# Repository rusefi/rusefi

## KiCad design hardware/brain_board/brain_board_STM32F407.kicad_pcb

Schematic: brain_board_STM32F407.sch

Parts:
BT1: BATTERY_CR2032; BATT_CR2032_MPD
C1: 20nF; C_0805
C2, C3, C21, C22: 18pF; C_0805
C4, C15, C17: 2u2F; C_0805
C5, C8: 0.01uF; C_0805
C6, C7, C16: 1uF; C_0805
C9, C10, C11, C12, C13, C14, C18, C20: 0.1uF; C_0805
C19: 4.7uF; C_0805
D1, D2, D3, D4, D7, D8, D11: BLUE_LED_0805; LED_0805
D5, D6, D9: PMEG2010EA; D_0805
F1002: FUSE; D_0805
FB1: FILTER; R_0805
G1: LOGO; LOGO_F
J1: MINI-USB-5P-3400020P1
J2: MINI-USB-5P-3400020P1V; MINI-USB_RCTP_V-T_B
JP1, JP2, JP3, JP4: JUMPER; Pin_Header_Straight_1x02_Pitch2.54mm
JP5: JUMPER3; Pin_Header_Straight_1x03_Pitch2.54mm
P1, P2: CONN_25X2; Pin_Header_Straight_2x25_Pitch2.54mm
P3: CONN_2; Pin_Header_Straight_1x02_Pitch2.54mm
P4: CONN_02X05; IDC_Header_Straight_10pins
P5, P6: CONN_01X03; Pin_Header_Angled_1x03
R1, R3, R4: 10k; R_0805
R2: 100R; R_0805
R5: 330R; R_0805
R6, R7, R8, R9: 680R; R_0805
R10: 47R; R_0805
R11, R12, R13: 1k; R_0805
R14: 100k; R_0805
SW1, SW2: SW_PUSH; TL-1105
U1: STM32F407VG; LQFP-100_14x14mm_Pitch0.5mm
U2: NUF2101MT1G; SOT-457
U3: LM2937; SOT223
X1: CRYSTAL; HC-49V
X2: CRYSTAL(MC306); MC-306

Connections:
/3V: D9.2 (K), P2.5, P2.6
/5V: C18.2, C19.1, D5.2 (K), D6.2 (K), F1002.1, F1002.2, P2.3, P2.4, P4.1, P4.2, U3.1 (Vin)
/BOOT0: P2.21, R4.2, U1.94 (BOOT0)
/D+: J1.3 (D+), J2.3 (D+), U2.6 (D+)
/D-: J1.2 (D-), J2.2 (D-), U2.4 (D-)
/NRST: C1.2, P1.6, P4.9, R3.2, SW1.1, U1.14 (NRST)
/PA0: P1.12, R5.1, U1.23 (PA0/WKUP/USART2_CTS/UART4_TX/ETH_MII_CR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)
/PA1: P1.11, U1.24 (PA1/USART2_RTS/UART4_RX/ETH_RMII_REF_CL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)
/PA2: P1.14, U1.25 (PA2/USART2_TX/TIM5_CH3/TIM9_CH1/TIM2_CH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)
/PA3: P1.13, U1.26 (PA3/USART2_RX/TIM5_CH4/TIM9_CH2/TIM2_CH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)
/PA4: P1.16, U1.29 (PA4/SPI1_NSS/SPI3_NSS/USART2_CK/DCMI_HS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)
/PA5: P1.15, U1.30 (PA5/SPI1_SCK/OTG_HS_ULPI_CK/TIM2_CH1_ET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)
/PA6: P1.18, U1.31 (PA6/SPI1_MISO/TIM8_BKIN/TIM13_CH1/DCMI_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)
/PA7: P1.17, U1.32 (PA7/SPI1_MOSI/TIM8_CH1N/TIM14_CH1/TIM3_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)
/PA8: P2.43, U1.67 (PA8/MCO1/USART1_CK/TIM1_CH1/I2C3_SCL/OT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)
/PA9: D6.1 (A), J1.1 (VBUS), J2.1 (VBUS), P2.44, R12.2, U1.68 (PA9/USART1_TX/TIM1_CH2/I2C3_SMBA/DCMI_D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), U2.5 (Vbus)
/PA10: P2.41, U1.69 (PA10/USART1_RX/TIM1_CH3/OTG_FS_ID/DCMI_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)
/PA11: U1.70 (PA11/USART1_CTS/CAN1_RX/TIM1_CH4_/OTG_F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), U2.3 (D-out)
/PA12: U1.71 (PA12/USART1_RTS/CAN1_TX/TIM1_ETR/OTG_FS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), U2.1 (D+out)
/PA13: P2.42, P4.10, U1.72 (PA13/JTMS/SWDIO/EVENTOUT)
/PA14: P2.39, P4.6, U1.76 (PA14/JTCK/SWCLK/EVENTOUT)
/PA15: P2.40, U1.77 (PA15/JTDI/SPI3_NSS/I2S3_WS/TIM2_CH1_ETR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)
/PB0: P1.22, U1.35 (PB0/TIM3_CH3/TIM8_CH2N/OTG_HS_ULPI_D1/E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)
/PB1: P1.21, U1.36 (PB1/TIM3_CH4/TIM8_CH3N/OTG_HS_ULPI_D2/E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)
/PB2: P1.24, U1.37 (PB2/BOOT1/EVENTOUT)
/PB3: P2.28, P4.5, P6.3, U1.89 (PB3/JTDO/TRACESWO/SPI3_SCK/I2S3_CK/TIM2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)
/PB4: P2.25, P5.1, U1.90 (PB4/NJTRST/SPI3_MISO/TIM3_CH1/SPI1_MISO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)
/PB5: P2.26, P5.2, U1.91 (PB5/I2C1_SMBA/CAN2_RX/OTG_HS_ULPI_D7/ET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)
/PB6: P2.23, U1.92 (PB6/I2C1_SCL/TIM4_CH1/CAN2_TX/DCMI_D5/U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)
/PB7: P2.24, U1.93 (PB7/I2C1_SDA/FSMC_NL/DCMI_VSYNC/USART1_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)
/PB8: P2.19, U1.95 (PB8/TIM4_CH3/SDIO_D4/TIM10_CH1/DCMI_D6/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)
/PB9: P2.20, U1.96 (PB9/SPI2_NSS/I2S2_WS/TIM4_CH4/TIM11_CH1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)
/PB10: P1.34, U1.47 (PB10/SPI2_SCK/I2S2_CK/I2C2_SCL/USART3_T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)
/PB11: P1.35, U1.48 (PB11/I2C2_SDA/USART3_RX/OTG_HS_ULPI_D4/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)
/PB12: P1.36, U1.51 (PB12/SPI2_NSS/I2S2_WS/I2C2_SMBA/USART3_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)
/PB13: P1.37, U1.52 (PB13/SPI2_SCK/I2S2_CK/USART3_CTS/TIM1_C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)
/PB14: P1.38, U1.53 (PB14/SPI2_MISO/TIM1_CH2N/TIM12_CH1/OTG_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)
/PB15: P1.39, U1.54 (PB15/SPI2_MOSI/I2S2_SD/TIM1_CH3N/TIM8_C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)
/PC0: P1.8, U1.15 (PC0/OTG_HS_ULPI_STP/EVENTOUT)
/PC1: P1.7, U1.16 (PC1/ETH_MDC/_EVENTOUT)
/PC2: P1.10, U1.17 (PC2/SPI2_MISO/OTG_HS_ULPI_DIR/ETH_MII_T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)
/PC3: P1.9, U1.18 (PC3/SPI2_MOSI/I2S2_SD/OTG_HS_ULPI_NXT/E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)
/PC4: P1.20, U1.33 (PC4/ETH_RMII_RX_D0/ETH_MII_RX_D0/EVENTO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)
/PC5: P1.19, U1.34 (PC5/ETH_RMII_RX_D1/ETH_MII_RX_D1/EVENTO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)
/PC6: P2.47, U1.63 (PC6/I2S2_MCK/TIM8_CH1/SDIO_D6/USART6_TX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)
/PC7: P2.48, U1.64 (PC7/I2S3_MCK/TIM8_CH2/SDIO_D7/USART6_RX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)
/PC8: P2.45, U1.65 (PC8/TIM8_CH3/SDIO_D0/TIM3_CH3/USART6_CK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)
/PC9: P2.46, U1.66 (PC9/I2S_CKIN/MCO2/TIM8_CH4/SDIO_D1/I2C3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)
/PC10: P2.37, U1.78 (PC10/SPI3_SCK/I2S3_CK/UART4_TX/SDIO_D2/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)
/PC11: P2.38, U1.79 (PC11/UART4_RX/SPI3_MISO/SDIO_D3/DCMI_D4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)
/PC12: P2.35, U1.80 (PC12/UART5_TX/SDIO_CK/DCMI_D9/SPI3_MOSI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)
/PC13: P2.12, U1.7 (PC13/EVENTOUT)
/PD0: P2.36, U1.81 (PD0/FSMC_D2/CAN1_RX/EVENTOUT)
/PD1: P2.33, U1.82 (PD1/FSMC_D3/CAN1_TX/EVENTOUT)
/PD2: P2.34, U1.83 (PD2/TIM3_ETR/UART5_RX/SDIO_CMD/DCMI_D11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)
/PD3: P2.31, U1.84 (PD3/FSMC_CLK/USART2_CTS/EVENTOUT)
/PD4: P2.32, P6.2, U1.85 (PD4/FSMC_NOE/USART2_RTS/EVENTOUT)
/PD5: P2.29, U1.86 (PD5/FSMC_NWE/USART2_TX/EVENTOUT)
/PD6: P2.30, U1.87 (PD6/FSMC_NWAIT/USART2_RX/EVENTOUT)
/PD7: P2.27, U1.88 (PD7/USART2_CK/FSMC_NE1/FSMC_NCE2/EVENTO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)
/PD8: P1.40, U1.55 (PD8/FSMC_D13/USART3_TX/EVENTOUT)
/PD9: P1.41, U1.56 (PD9/FSMC_D14/USART3_RX/EVENTOUT)
/PD10: P1.42, U1.57 (PD10/FSMC_D15/USART3_CK/EVENTOUT)
/PD11: P1.43, U1.58 (PD11/FSMC_CLE/FSMC_A16/USART3_CTS/EVENT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)
/PD12: JP1.1, P1.44, U1.59 (PD12/FSMC_ALE/FSMC_A17/TIM4_CH1/USART3_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)
/PD13: JP2.1, P1.45, U1.60 (PD13/FSMC_A18/TIM4_CH2/EVENTOUT)
/PD14: JP3.1, P1.46, U1.61 (PD14/FSMC_D0/TIM4_CH3/EVENTOUT/_EVENTOUT)
/PD15: JP4.1, P1.47, U1.62 (PD15/FSMC_D1/TIM4_CH4/EVENTOUT)
/PE0: P2.17, U1.97 (PE0/TIM4_ETR/FSMC_NBL0/DCMI_D2/EVENTOUT)
/PE1: P2.18, U1.98 (PE1/FSMC_NBL1/DCMI_D3/EVENTOUT)
/PE2: P2.15, U1.1 (PE2/TRACECLK/FSMC_A23/ETH_MII_TXD3/EVEN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)
/PE3: P2.16, U1.2 (PE3/TRACED0/FSMC_A19/EVENTOUT)
/PE4: P2.13, U1.3 (PE4/TRACED1/FSMC_A20/DCMI_D4/EVENTOUT)
/PE5: P2.14, U1.4 (PE5/TRACED2/FSMC_A21/TIM9_CH1/DCMI_D6/E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)
/PE6: P2.11, U1.5 (PE6/TRACED3_/_FSMC_A22/TIM9_CH2/DCMI_D7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)
/PE7: P1.25, U1.38 (PE7/FSMC_D4/TIM1_ETR/EVENTOUT)
/PE8: P1.26, U1.39 (PE8/FSMC_D5/TIM1_CH1N/EVENTOUT)
/PE9: P1.27, U1.40 (PE9/FSMC_D6/TIM1_CH1/EVENTOUT)
/PE10: P1.28, U1.41 (PE10/FSMC_D7/TIM1_CH2N/EVENTOUT)
/PE11: P1.29, U1.42 (PE11/FSMC_D8/TIM1_CH2/EVENTOUT)
/PE12: P1.30, U1.43 (PE12/FSMC_D9/TIM1_CH3N/EVENTOUT)
/PE13: P1.31, U1.44 (PE13/FSMC_D10/TIM1_CH3/EVENTOUT)
/PE14: P1.32, U1.45 (PE14/FSMC_D11/TIM1_CH4/EVENTOUT)
/PE15: P1.33, U1.46 (PE15/FSMC_D12/TIM1_BKIN/EVENTOUT)
/Shield: C20.1, J1.6 (SHIELD), J2.6 (SHIELD), R14.1
/VDD: C4.1, C9.2, C10.2, C11.2, C12.2, C13.2, C14.2, C16.2, D9.1 (A), FB1.2, JP5.1, P1.3, P1.4, P2.22, P4.3, P4.4, P5.3, R3.1, R13.2, SW2.2, U1.11 (VDD), U1.19 (VDD), U1.28 (VDD), U1.50 (VDD), U1.75 (VDD), U1.100 (VDD), U3.3 (Vout)
GND: BT1.2 (-), C1.1, C2.2, C3.2, C5.1, C6.1, C7.1, C8.1, C9.1, C10.1, C11.1, C12.1, C13.1, C14.1, C15.2, C16.1, C17.2, C18.1, C19.2, C20.2, C21.1, C22.1, D1.2 (K), D2.2 (K), D3.2 (K), D4.2 (K), D7.2 (K), D8.2 (K), D11.2 (K), J1.5 (GND), J2.5 (GND), P1.1, P1.2, P1.5, P1.23, P1.49, P1.50, P2.1, P2.2, P2.49, P2.50, P3.2 (PM), P4.7, P4.8, P6.1, R1.2, R4.1, R14.2, SW1.2, U1.10 (VSS), U1.20 (VSSA), U1.27 (VSS), U1.74 (VSS), U1.99 (VSS), U2.2 (GND), U3.2 (GND), U3.4
unnamed: BT1.1 (+), JP5.3
unnamed: C2.1, U1.12 (PH0/OSC_IN/EVENTOUT), X1.2
unnamed: C3.1, U1.13 (PH1/OSC_OUT/EVENTOUT), X1.1
unnamed: C4.2, R2.1
unnamed: C5.2, C6.2, R10.2, U1.21 (VREF+)
unnamed: C7.2, C8.2, FB1.1, R10.1, U1.22 (VDDA)
unnamed: C15.1, U1.49 (VCAP_1)
unnamed: C17.1, U1.73 (VCAP_2)
unnamed: C21.2, U1.8 (PC14/OSC32_IN/EVENTOUT), X2.1
unnamed: C22.2, U1.9 (PC15/OSC32_OUT/EVENTOUT), X2.4
unnamed: D1.1 (A), R6.1
unnamed: D2.1 (A), R7.1
unnamed: D3.1 (A), R8.1
unnamed: D4.1 (A), R9.1
unnamed: D5.1 (A), P3.1, R11.2
unnamed: D7.1 (A), R11.1
unnamed: D8.1 (A), R12.1
unnamed: D11.1 (A), R13.1
unnamed: JP1.2, R6.2
unnamed: JP2.2, R7.2
unnamed: JP3.2, R8.2
unnamed: JP4.2, R9.2
unnamed: JP5.2, U1.6 (VBAT)
unnamed: R1.1, R2.2, R5.2, SW2.1

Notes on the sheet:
Left conn
Right conn
Reset
User & Wake-UP Button
Green
Orange
Red
Blue
Ext 5V in
SWD
USB power
Ext power
Power line ON
3.3v
8MHz
32.768kHz
RST GND SWIM 3.3V 5.0V
SWDIO GND SWCLK 3.3V 5.0V
SD Card

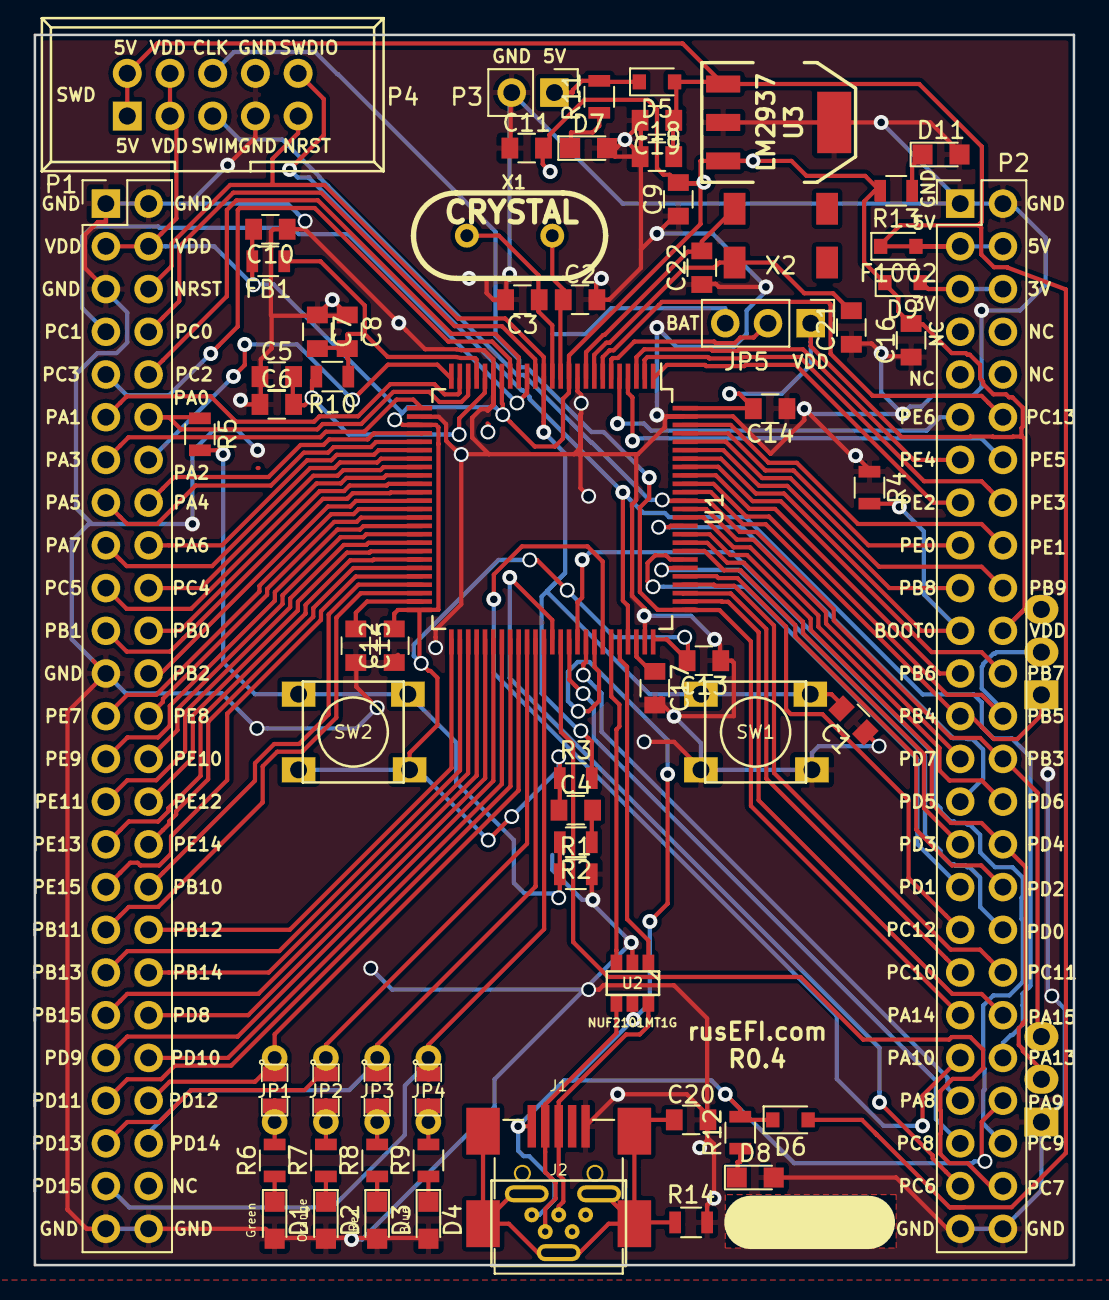
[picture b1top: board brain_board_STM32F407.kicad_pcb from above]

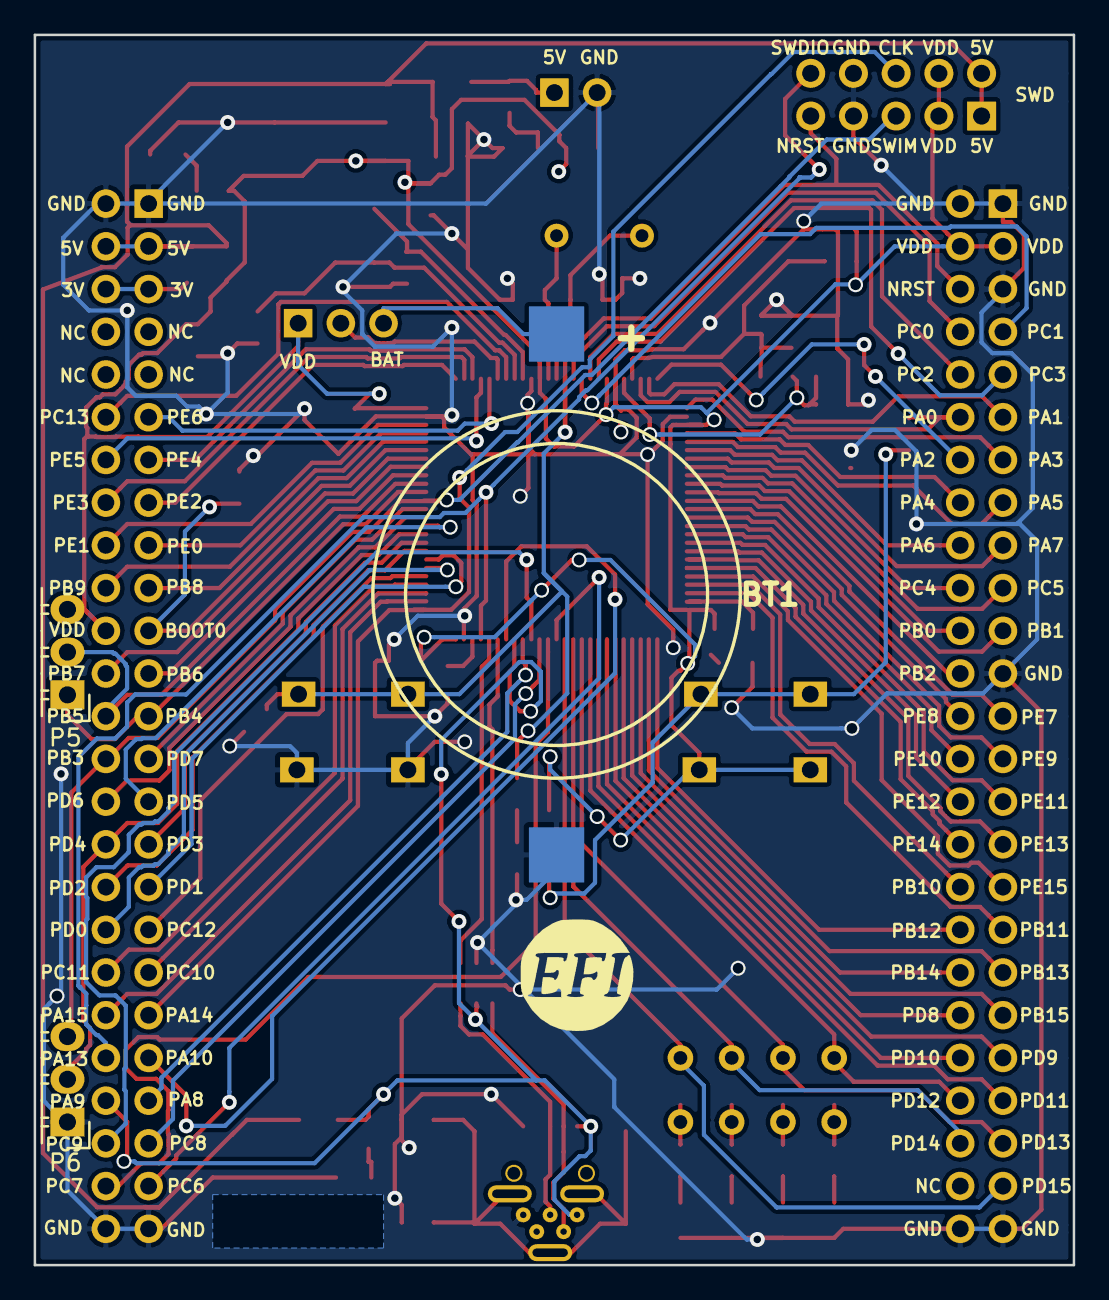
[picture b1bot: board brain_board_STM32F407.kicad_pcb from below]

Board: 2 copper layers, 61.8 x 73.2 mm, 70 parts (4 on the bottom side), 111 nets.

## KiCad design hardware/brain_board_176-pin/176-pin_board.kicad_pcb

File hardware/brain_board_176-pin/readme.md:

Brain board stm 176 pin

[Known issues](known_issues.txt)

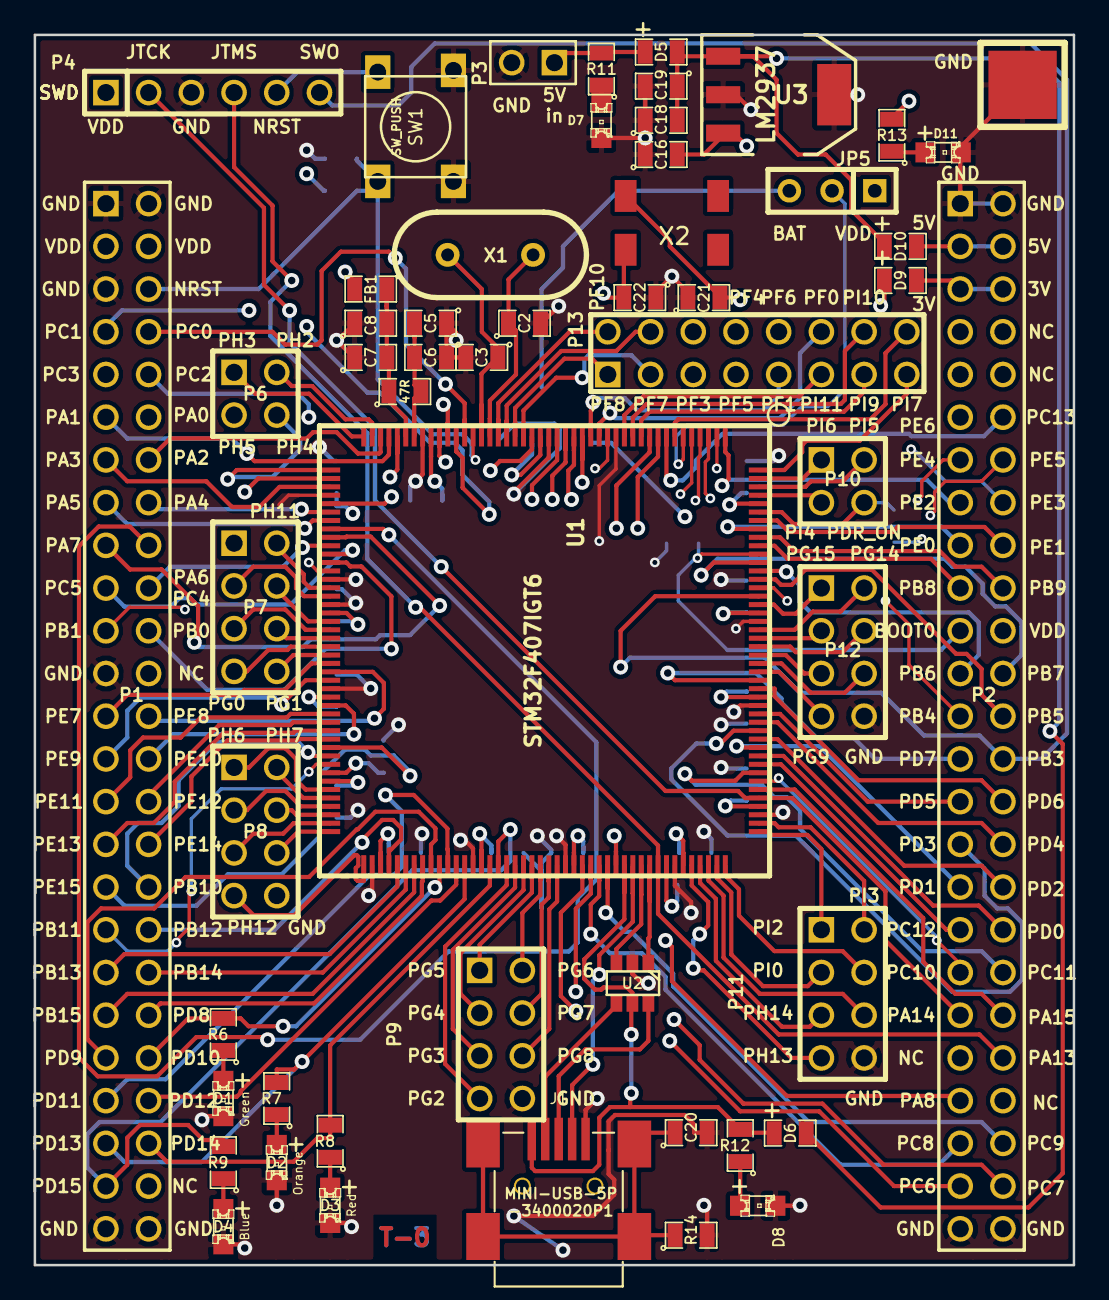
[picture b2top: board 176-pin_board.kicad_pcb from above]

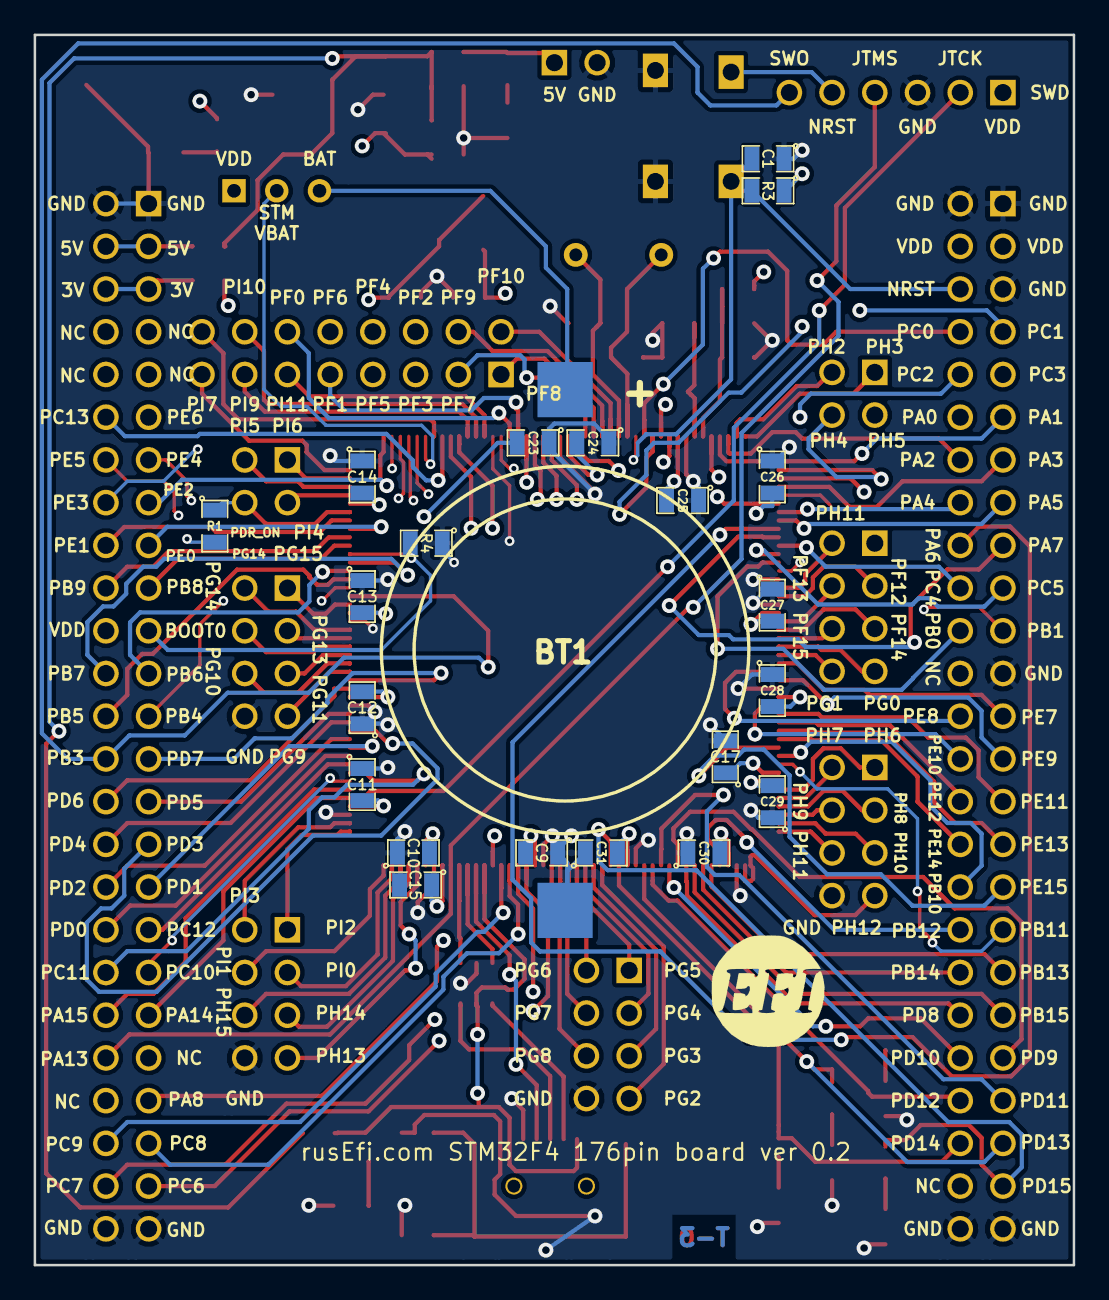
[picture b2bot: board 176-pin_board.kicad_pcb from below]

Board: 4 copper layers, 61.8 x 73.2 mm, 77 parts (23 on the bottom side), 164 nets.

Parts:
BT1: BATTERY_CR2032; BATT_CR2032_MPD
C1: 0.02uF; SM0805
C2, C3, C21, C22: 18pF; SM0805
C5, C8: 0.01uF; SM0805
C6, C7, C16: 1uF; SM0805
C9, C10, C11, C12, C13, C14, C18, C20, C23, C24, C25, C26, C27, C28, C29, C30, C31: 0.1uF; SM0805
C15, C17: 2u2F; SM0805
C19: 4.7uF; SM0805
D1, D2, D3, D4, D7, D8, D11: LED_0805; LED-0805_A
D5, D6, D9, D10: DIODESCH; SM0805-diode
FB1: FILTER; SM0805
G1: LOGO; LOGO_F
J1: MINI-USB-5P-3400020P1
JP5: JUMPER3; SIL-3
P1, P2: CONN_25X2; PIN_ARRAY_25x2_A
P3: CONN_2; PIN_ARRAY_2_A
P4: CONN_6; PIN_ARRAY-6X1
P5: CONN_1; 1PIN_SMD
P6, P10: CONN_2X2; PIN_ARRAY_2X2
P7, P8, P9, P11, P12: CONN_4X2; pin_array_4x2
P13: CONN_8X2; pin_array_8x2
R1, R11, R12, R13: 1k; SM0805
R3, R4: 10k; SM0805
R6, R7, R8, R9: 680R; SM0805
R10: 47R; SM0805
R14: 100k; SM0805
SW1: SW_PUSH; TL-1105
U1: STM32F407IGT6; LQFP-176
U2: NUF2101MT1G; SOT-457
U3: LM2937; SOT223
X1: CRYSTAL; HC-49V
X2: CRYSTAL(MC306); MC-306

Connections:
/3.3V: D9.2, P2.5, P2.6
/5V: D10.2, P2.3, P2.4
/5Vi: C18.2, C19.1, D5.2, D6.2, D10.1, U3.1
/BOOT0: P2.21, R4.2, U1.166
/D+: J1.3, U2.6
/D-: J1.2, U2.4
/NRST: C1.2, P1.6, P4.5, R3.2, SW1.1, U1.31
/PA0: P1.12, U1.40
/PA1: P1.11, U1.41
/PA2: P1.14, U1.42
/PA3: P1.13, U1.47
/PA4: P1.16, U1.50
/PA5: P1.15, U1.51
/PA6: P1.18, U1.52
/PA7: P1.17, U1.53
/PA8: P2.43, U1.119
/PA9: D6.1, J1.1, R12.2, U1.120, U2.5
/PA10: J1.4, U1.121
/PA11: U1.122, U2.3
/PA12: U1.123, U2.1
/PA13: P2.42, P4.4, U1.124
/PA14: P2.39, P4.2, U1.137
/PA15: P2.40, U1.138
/PB0: P1.22, U1.56
/PB1: P1.21, U1.57
/PB3: P2.28, P4.6, U1.161
/PB4: P2.25, U1.162
/PB5: P2.26, U1.163
/PB6: P2.23, U1.164
/PB7: P2.24, U1.165
/PB8: P2.19, U1.167
/PB9: P2.20, U1.168
/PB10: P1.34, U1.79
/PB11: P1.35, U1.80
/PB12: P1.36, U1.92
/PB13: P1.37, U1.93
/PB14: P1.38, U1.94
/PB15: P1.39, U1.95
/PC0: P1.8, U1.32
/PC1: P1.7, U1.33
/PC2: P1.10, U1.34
/PC3: P1.9, U1.35
/PC4: P1.20, U1.54
/PC5: P1.19, U1.55
/PC6: P2.47, U1.115
/PC7: P2.48, U1.116
/PC8: P2.45, U1.117
/PC9: P2.46, U1.118
/PC10: P2.37, U1.139
/PC11: P2.38, U1.140
/PC12: P2.35, U1.141
/PC13: P2.12, U1.8
/PD0: P2.36, U1.142
/PD1: P2.33, U1.143
/PD2: P2.34, U1.144
/PD3: P2.31, U1.145
/PD4: P2.32, U1.146
/PD5: P2.29, U1.147
/PD6: P2.30, U1.150
/PD7: P2.27, U1.151
/PD8: P1.40, U1.96
/PD9: P1.41, U1.97
/PD10: P1.42, R6.2, U1.98
/PD11: P1.43, U1.99
/PD12: P1.44, U1.100
/PD13: P1.45, R7.2, U1.101
/PD14: P1.46, R8.2, U1.104
/PD15: P1.47, R9.2, U1.105
/PDR_ON: P10.4, R1.1, U1.171
/PE0: P2.17, U1.169
/PE1: P2.18, U1.170
/PE2: P2.15, U1.1
/PE3: P2.16, U1.2
/PE4: P2.13, U1.3
/PE5: P2.14, U1.4
/PE6: P2.11, U1.5
/PE7: P1.25, U1.68
/PE8: P1.26, U1.69
/PE9: P1.27, U1.70
/PE10: P1.28, U1.73
/PE11: P1.29, U1.74
/PE12: P1.30, U1.75
/PE13: P1.31, U1.76
/PE14: P1.32, U1.77
/PE15: P1.33, U1.78
/PF0: P13.12, U1.16
/PF1: P13.9, U1.17
/PF2: P13.6, U1.18
/PF3: P13.5, U1.19
/PF4: P13.8, U1.20
/PF5: P13.7, U1.21
/PF6: P13.10, U1.24
/PF7: P13.3, U1.25
/PF8: P13.1, U1.26
/PF9: P13.4, U1.27
/PF10: P13.2, U1.28
/PF11: P7.2, U1.59
/PF12: P7.3, U1.60
/PF13: P7.4, U1.63
/PF14: P7.5, U1.64
/PF15: P7.6, U1.65
/PG0: P7.7, U1.66
/PG1: P7.8, U1.67
/PG2: P9.7, U1.106
/PG3: P9.5, U1.107
/PG4: P9.3, U1.108
/PG5: P9.1, U1.109
/PG6: P9.2, U1.110
/PG7: P9.4, U1.111
/PG8: P9.6, U1.112
/PG9: P12.7, U1.152
/PG10: P12.6, U1.153
/PG11: P12.5, U1.154
/PG12: P12.4, U1.155
/PG13: P12.3, U1.156
/PG14: P12.2, U1.157
/PG15: P12.1, U1.160
/PH0: C2.1, U1.29, X1.2
/PH1: C3.1, U1.30, X1.1
/PH2: P6.2, U1.43
/PH3: P6.1, U1.44
/PH4: P6.4, U1.45
/PH5: P6.3, U1.46
/PH6: P8.1, U1.83
/PH7: P8.2, U1.84
/PH8: P8.3, U1.85
/PH9: P8.4, U1.86
/PH10: P8.5, U1.87
/PH11: P8.6, U1.88
/PH12: P8.7, U1.89
/PH13: P11.7, U1.128
/PH14: P11.5, U1.129
/PH15: P11.6, U1.130
/PI0: P11.3, U1.131
/PI1: P11.4, U1.132
/PI2: P11.1, U1.133
/PI3: P11.2, U1.134
/PI4: P10.3, U1.173
/PI5: P10.2, U1.174
/PI6: P10.1, U1.175
/PI7: P13.15, U1.176
/PI8: P13.16, U1.7
/PI9: P13.13, U1.11
/PI10: P13.14, U1.12
/PI11: P13.11, U1.13
/VBAT: JP5.2, U1.6
/VDD: C9.2, C10.2, C11.2, C12.2, C13.2, C14.2, C16.2, C23.2, C24.2, C25.2, C26.2, C27.2, C28.2, C29.2, C30.2, C31.2, D9.1, FB1.2, JP5.1, P1.3, P1.4, P2.22, P4.1, R1.2, R3.1, R13.2, U1.15, U1.23, U1.36, U1.49, U1.62, U1.72, U1.82, U1.91, U1.103, U1.114, U1.127, U1.136, U1.149, U1.159, U1.172, U3.3
GND: BT1.2, C1.1, C2.2, C3.2, C5.1, C6.1, C7.1, C8.1, C9.1, C10.1, C11.1, C12.1, C13.1, C14.1, C15.2, C16.1, C17.2, C18.1, C19.2, C20.2, C21.1, C22.1, C23.1, C24.1, C25.1, C26.1, C27.1, C28.1, C29.1, C30.1, C31.1, D1.2, D2.2, D3.2, D4.2, D7.2, D8.2, D11.2, J1.5, P1.1, P1.2, P1.5, P1.23, P1.49, P1.50, P2.1, P2.2, P2.49, P2.50, P3.2, P4.3, P5.1, P8.8, P9.8, P11.8, P12.8, R4.1, R14.2, SW1.2, U1.14, U1.22, U1.37, U1.48, U1.58, U1.61, U1.71, U1.90, U1.102, U1.113, U1.126, U1.135, U1.148, U1.158, U2.2, U3.2, U3.4
unnamed: C7.2, C8.2, FB1.1, R10.1, U1.39
unnamed: D11.1, R13.1
unnamed: D2.1, R7.1
unnamed: D1.1, R6.1
unnamed: C5.2, C6.2, R10.2, U1.38
unnamed: D3.1, R8.1
unnamed: D5.1, P3.1, R11.2
unnamed: BT1.1, JP5.3
unnamed: D4.1, R9.1
unnamed: D7.1, R11.1
unnamed: D8.1, R12.1
unnamed: C20.1, J1.6, R14.1
unnamed: C21.2, U1.9, X2.4
unnamed: C22.2, U1.10, X2.1
unnamed: C15.1, U1.125
unnamed: C17.1, U1.81

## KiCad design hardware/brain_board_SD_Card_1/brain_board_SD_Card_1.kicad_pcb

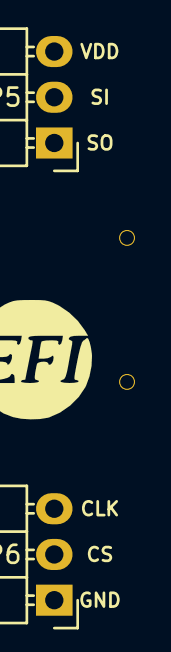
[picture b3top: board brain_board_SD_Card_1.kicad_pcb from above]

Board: 2 copper layers, 4 parts (1 on the bottom side), 6 nets, no tracks yet.

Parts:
G1: LOGO; LOGO_F
P5, P6: CONN_01X03; Pin_Header_Angled_1x03
P352: MICRO-SDCARD-CONNECTOR-3300060P1

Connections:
/3.3V: P5.3, P352.4
/CS_SD_MODULE: P6.2, P352.2
/SPI_MISO: P5.1, P352.7
/SPI_MOSI: P5.2, P352.3
/SPI_SCK: P6.3, P352.5
GND: P6.1, P352.6, P352.G1, P352.G2, P352.G3, P352.G4

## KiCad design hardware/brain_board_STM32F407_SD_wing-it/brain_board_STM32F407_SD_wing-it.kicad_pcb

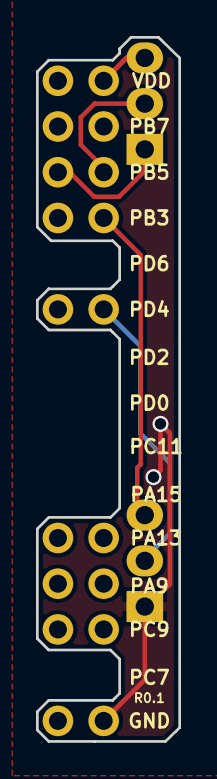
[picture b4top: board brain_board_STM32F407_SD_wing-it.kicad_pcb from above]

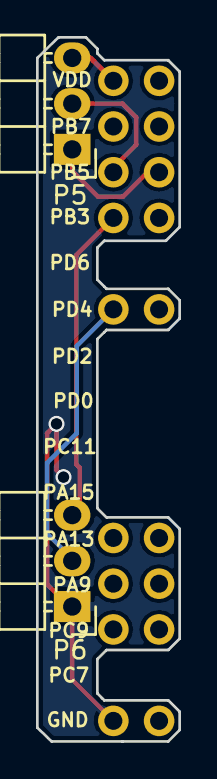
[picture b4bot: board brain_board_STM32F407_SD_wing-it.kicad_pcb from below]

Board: 2 copper layers, 7.9 x 39.1 mm, 8 parts (2 on the bottom side), 6 nets.

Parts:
P1: CONN_02X04; Pin_Header_Straight_2x04_Pitch2.54mm
P2: CONN_02X03; Pin_Header_Straight_2x03_Pitch2.54mm
P5, P6: CONN_01X03; Pin_Header_Angled_1x03
P7, P8, P11, P12: CONN_01X01; Pin_Header_Straight_1x01_Pitch2.54mm

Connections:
/PB3: P1.8, P6.3
/PB4: P1.5, P5.1
/PB5: P1.6, P5.2
/PD4: P6.2, P7.1
/VDD: P1.2, P5.3
GND: P6.1, P8.1

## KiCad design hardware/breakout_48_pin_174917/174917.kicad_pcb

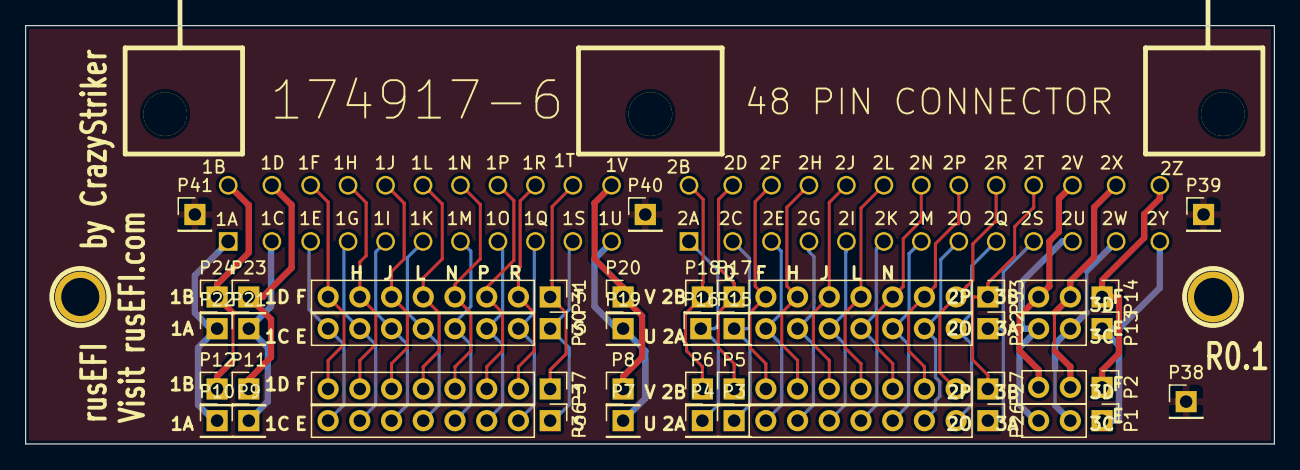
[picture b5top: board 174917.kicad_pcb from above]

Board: 2 copper layers, 100.0 x 33.5 mm, 39 parts (0 on the bottom side), 49 nets.

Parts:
1PIN, 1PIN#2: P***; 1pin
P1, P2, P13, P14: CONN_3; PinHeader_1x03_P2.54mm_Vertical
P3, P4, P5, P6, P7, P8, P9, P10, P11, P12, P15, P16, P17, P18, P19, P20, P21, P22, P23, P24, P38, P39, P40, P41: CONN_1; PinHeader_1x01_P2.54mm_Vertical
P25: 174917
P26, P27, P30, P31, P32, P33, P36, P37: CONN_8; PinHeader_1x08_P2.54mm_Vertical

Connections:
GND: P38.1, P39.1, P40.1, P41.1
unnamed: P1.1, P13.1
unnamed: P1.2, P13.2
unnamed: P1.3, P13.3
unnamed: P10.1, P22.1
unnamed: P11.1, P23.1
unnamed: P12.1, P24.1
unnamed: P2.1, P14.1
unnamed: P2.2, P14.2
unnamed: P2.3, P14.3
unnamed: P3.1, P15.1
unnamed: P4.1, P16.1
unnamed: P5.1, P17.1
unnamed: P6.1, P18.1
unnamed: P7.1, P19.1
unnamed: P8.1, P20.1
unnamed: P9.1, P21.1
unnamed: P26.1, P32.1
unnamed: P26.3, P32.3
unnamed: P26.4, P32.4
unnamed: P26.5, P32.5
unnamed: P26.6, P32.6
unnamed: P26.7, P32.7
unnamed: P26.8, P32.8
unnamed: P27.1, P33.1
unnamed: P27.2, P33.2
unnamed: P27.3, P33.3
unnamed: P27.4, P33.4
unnamed: P27.5, P33.5
unnamed: P27.6, P33.6
unnamed: P27.7, P33.7
unnamed: P27.8, P33.8
unnamed: P30.1, P36.1
unnamed: P30.2, P36.2
unnamed: P30.3, P36.3
unnamed: P30.4, P36.4
unnamed: P30.5, P36.5
unnamed: P30.6, P36.6
unnamed: P30.7, P36.7
unnamed: P30.8, P36.8
unnamed: P31.1, P37.1
unnamed: P31.2, P37.2
unnamed: P31.3, P37.3
unnamed: P31.4, P37.4
unnamed: P31.5, P37.5
unnamed: P31.6, P37.6
unnamed: P31.7, P37.7
unnamed: P31.8, P37.8
unnamed: P26.2, P32.2

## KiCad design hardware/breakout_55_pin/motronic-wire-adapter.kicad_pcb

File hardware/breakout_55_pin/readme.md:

This version of the 55 pin seems to be used by Bosch on BMW/GM ECUs around 1.5.x

See [here](../963063-15_55_pin_connector) for another version of connector

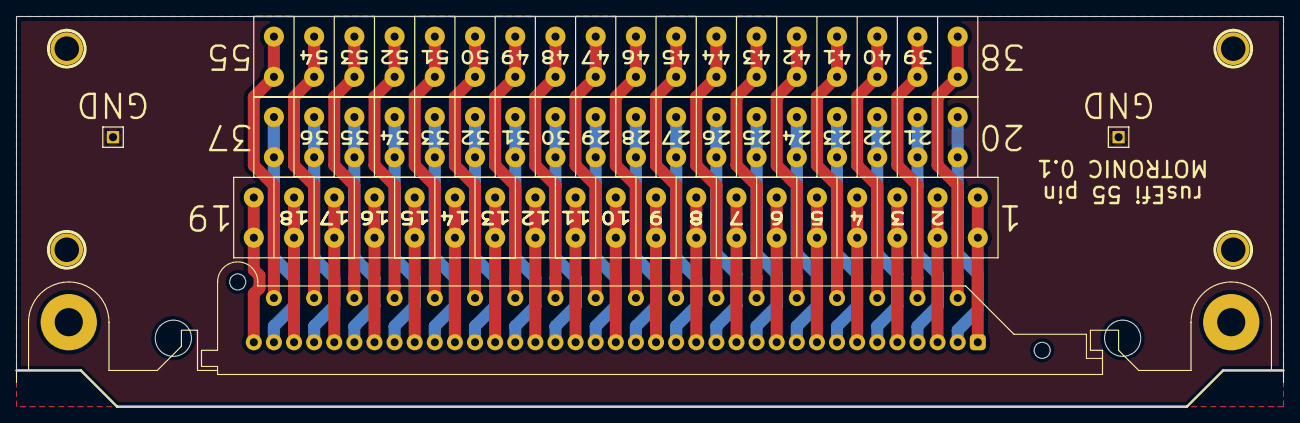
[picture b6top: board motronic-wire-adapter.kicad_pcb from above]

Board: 2 copper layers, 157.5 x 48.5 mm, 10 parts (0 on the bottom side), 56 nets.

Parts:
1PIN, 1PIN#2, 1PIN#3, 1PIN#4: P***; 1pin
P1: MOTRONIC; 55pin_china_bosch_motronic
P2: CONN_19; CON19X5
P3, P4: CONN_18; CON18X5
P5, P6: CONN_1; PIN_ARRAY_1

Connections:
GND: P5.1, P6.1
unnamed: P1.11, P2.11
unnamed: P1.1, P2.1
unnamed: P1.2, P2.2
unnamed: P1.3, P2.3
unnamed: P1.4, P2.4
unnamed: P1.5, P2.5
unnamed: P1.6, P2.6
unnamed: P1.7, P2.7
unnamed: P1.8, P2.8
unnamed: P1.9, P2.9
unnamed: P1.10, P2.10
unnamed: P1.55, P4.18
unnamed: P1.12, P2.12
unnamed: P1.13, P2.13
unnamed: P1.14, P2.14
unnamed: P1.15, P2.15
unnamed: P1.16, P2.16
unnamed: P1.17, P2.17
unnamed: P1.18, P2.18
unnamed: P1.19, P2.19
unnamed: P1.20, P3.1
unnamed: P1.21, P3.2
unnamed: P1.44, P4.7
unnamed: P1.34, P3.15
unnamed: P1.35, P3.16
unnamed: P1.36, P3.17
unnamed: P1.37, P3.18
unnamed: P1.38, P4.1
unnamed: P1.39, P4.2
unnamed: P1.40, P4.3
unnamed: P1.41, P4.4
unnamed: P1.42, P4.5
unnamed: P1.43, P4.6
unnamed: P1.22, P3.3
unnamed: P1.45, P4.8
unnamed: P1.46, P4.9
unnamed: P1.47, P4.10
unnamed: P1.48, P4.11
unnamed: P1.49, P4.12
unnamed: P1.50, P4.13
unnamed: P1.51, P4.14
unnamed: P1.52, P4.15
unnamed: P1.53, P4.16
unnamed: P1.54, P4.17
unnamed: P1.33, P3.14
unnamed: P1.23, P3.4
unnamed: P1.24, P3.5
unnamed: P1.25, P3.6
unnamed: P1.26, P3.7
unnamed: P1.27, P3.8
unnamed: P1.28, P3.9
unnamed: P1.29, P3.10
unnamed: P1.30, P3.11
unnamed: P1.31, P3.12
unnamed: P1.32, P3.13

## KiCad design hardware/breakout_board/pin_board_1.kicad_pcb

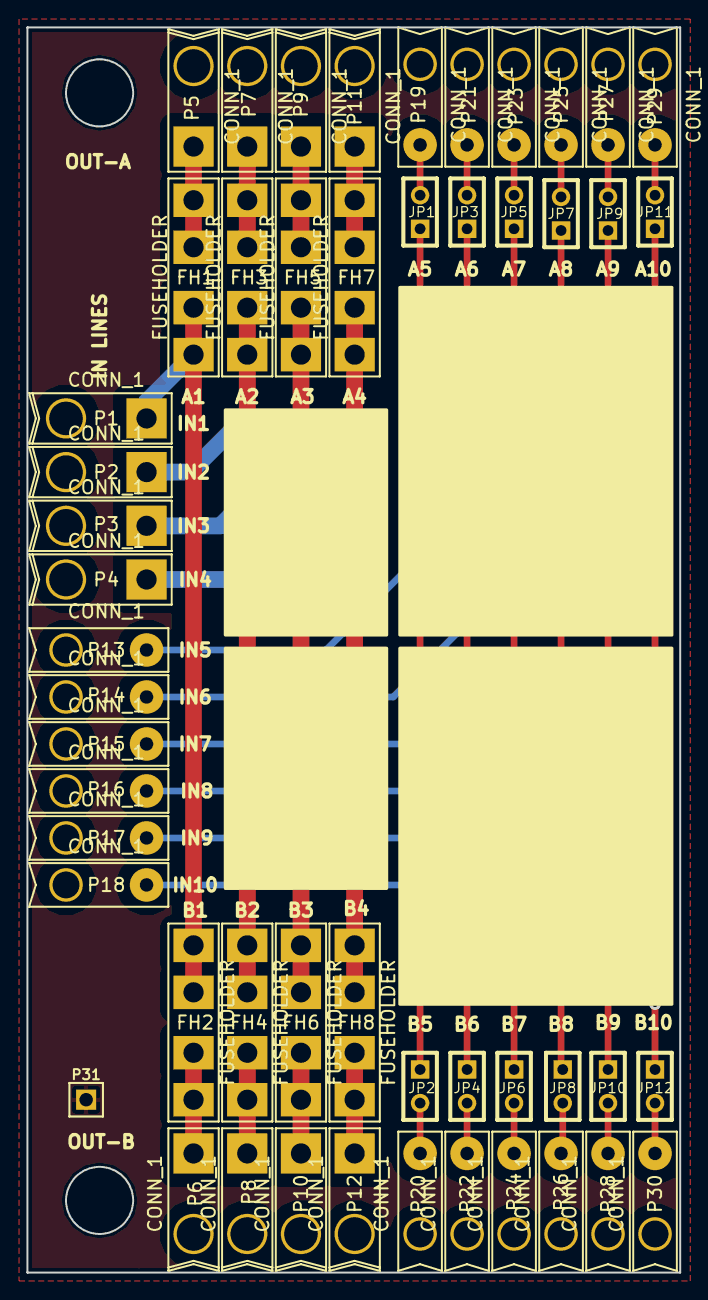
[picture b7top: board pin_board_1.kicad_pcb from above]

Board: 2 copper layers, 49.4 x 94.2 mm, 51 parts (0 on the bottom side), 30 nets.

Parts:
FH1, FH2, FH3, FH4, FH5, FH6, FH7, FH8: FUSEHOLDER
JP1, JP2, JP3, JP4, JP5, JP6, JP7, JP8, JP9, JP10, JP11, JP12: JUMPER; JUMPER-2
P1, P2, P3, P4, P5, P6, P7, P8, P9, P10, P11, P12: CONN_1; PIN_1_16AWG
P13, P14, P15, P16, P17, P18, P19, P20, P21, P22, P23, P24, P25, P26, P27, P28, P29, P30: CONN_1; PIN_1_20AWG
P31: CONN_1; PIN_ARRAY_1

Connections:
unnamed: JP8.2, P26.1
unnamed: JP7.2, P25.1
unnamed: JP7.1, JP8.1, P16.1
unnamed: JP3.2, P21.1
unnamed: JP4.2, P22.1
unnamed: JP3.1, JP4.1, P14.1
unnamed: JP5.1, JP6.1, P15.1
unnamed: JP6.2, P24.1
unnamed: JP5.2, P23.1
unnamed: JP11.2, P29.1
unnamed: JP12.2, P30.1
unnamed: JP11.1, JP12.1, P18.1
unnamed: JP10.2, P28.1
unnamed: JP9.2, P27.1
unnamed: JP9.1, JP10.1, P17.1
unnamed: JP1.2, P19.1
unnamed: JP2.2, P20.1
unnamed: FH3.1, FH4.1, P2.1
unnamed: FH4.2, P8.1
unnamed: FH3.2, P7.1
unnamed: FH1.1, FH2.1, P1.1
unnamed: FH2.2, P6.1
unnamed: FH1.2, P5.1
unnamed: JP1.1, JP2.1, P13.1
unnamed: FH7.1, FH8.1, P4.1
unnamed: FH8.2, P12.1
unnamed: FH7.2, P11.1
unnamed: FH5.1, FH6.1, P3.1
unnamed: FH6.2, P10.1
unnamed: FH5.2, P9.1
